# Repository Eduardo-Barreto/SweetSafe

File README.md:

# SweetSafe

Este repositório contém os arquivos do esquemático e da PCB do projeto SweetSafe, um "cofre" de doces com Raspberry Pi Pico. Inclui uma descrição dos componentes utilizados e instruções para montagem.

O funcionamento do SweetSafe é simples: a Raspberry Pi Pico controla um eletroímã que mantém a caixa de doces fechada. Quando um pagamento é realizado com sucesso, a Raspberry Pi Pico desativa o eletroímã, permitindo que a caixa seja aberta. Neste momento, LEDs indicam visualmente que a caixa está destravada, enquanto um buzzer emite um som indicando o sucesso da transação. Caso haja uma tentativa de acesso não autorizada, um sensor de fim de curso detecta a abertura da caixa e aciona um alarme, enquanto a Raspberry Pi Pico envia uma notificação aos servidores. Assim, o SweetSafe não apenas mantém os doces seguros, mas também fornece um sistema de monitoramento eficiente para proteger seu conteúdo.

## Pastas e Arquivos

- **kicad/**: Contém os arquivos de esquemático e PCB do projeto, bem como o principal do KiCad

  - `SweetSafe.kicad_pro`: Arquivo do KiCad
  - `SweetSafe.kicad_sch`: Esquemático do projeto
  - `SweetSafe.kicad_pcb`: Layout para a PCB do projeto

- **BOM.csv**: Lista de materiais do projeto.

- **images/**: Contém as imagens do projeto

## Imagens

### Esquemático

### PCB

### Visão 3D

3D com RayTracing (porque é maneiro)

## BOM (Bill of Materials)

| Designator           | Footprint                                          | Quantity |
| -------------------- | -------------------------------------------------- | -------- |
| Switch fim de curso  | SW_MS0850502F030P1A                                | 1        |
| Resistor 220 ohms    | R_Axial_DIN0414_L11.9mm_D4.5mm_P15.24mm_Horizontal | 2        |
| Resistor 10k ohms    | R_Axial_DIN0414_L11.9mm_D4.5mm_P15.24mm_Horizontal | 1        |
| Buzzer               | Buzzer_15x7.5RM7.6                                 | 1        |
| Transistor NPN BC337 | TO-92_Inline_Wide                                  | 1        |
| Raspberry Pi Pico W  | RPi_Pico_SMD_TH                                    | 1        |
| Conector Barrel Jack | BarrelJack_Horizontal                              | 1        |
| Header Fêmea 1x02    | PinSocket_1x02_P2.54mm_Horizontal                  | 3        |

## Gerbers

Os arquivos Gerber estão disponíveis na última release e na pasta `/kicad/gerbers`

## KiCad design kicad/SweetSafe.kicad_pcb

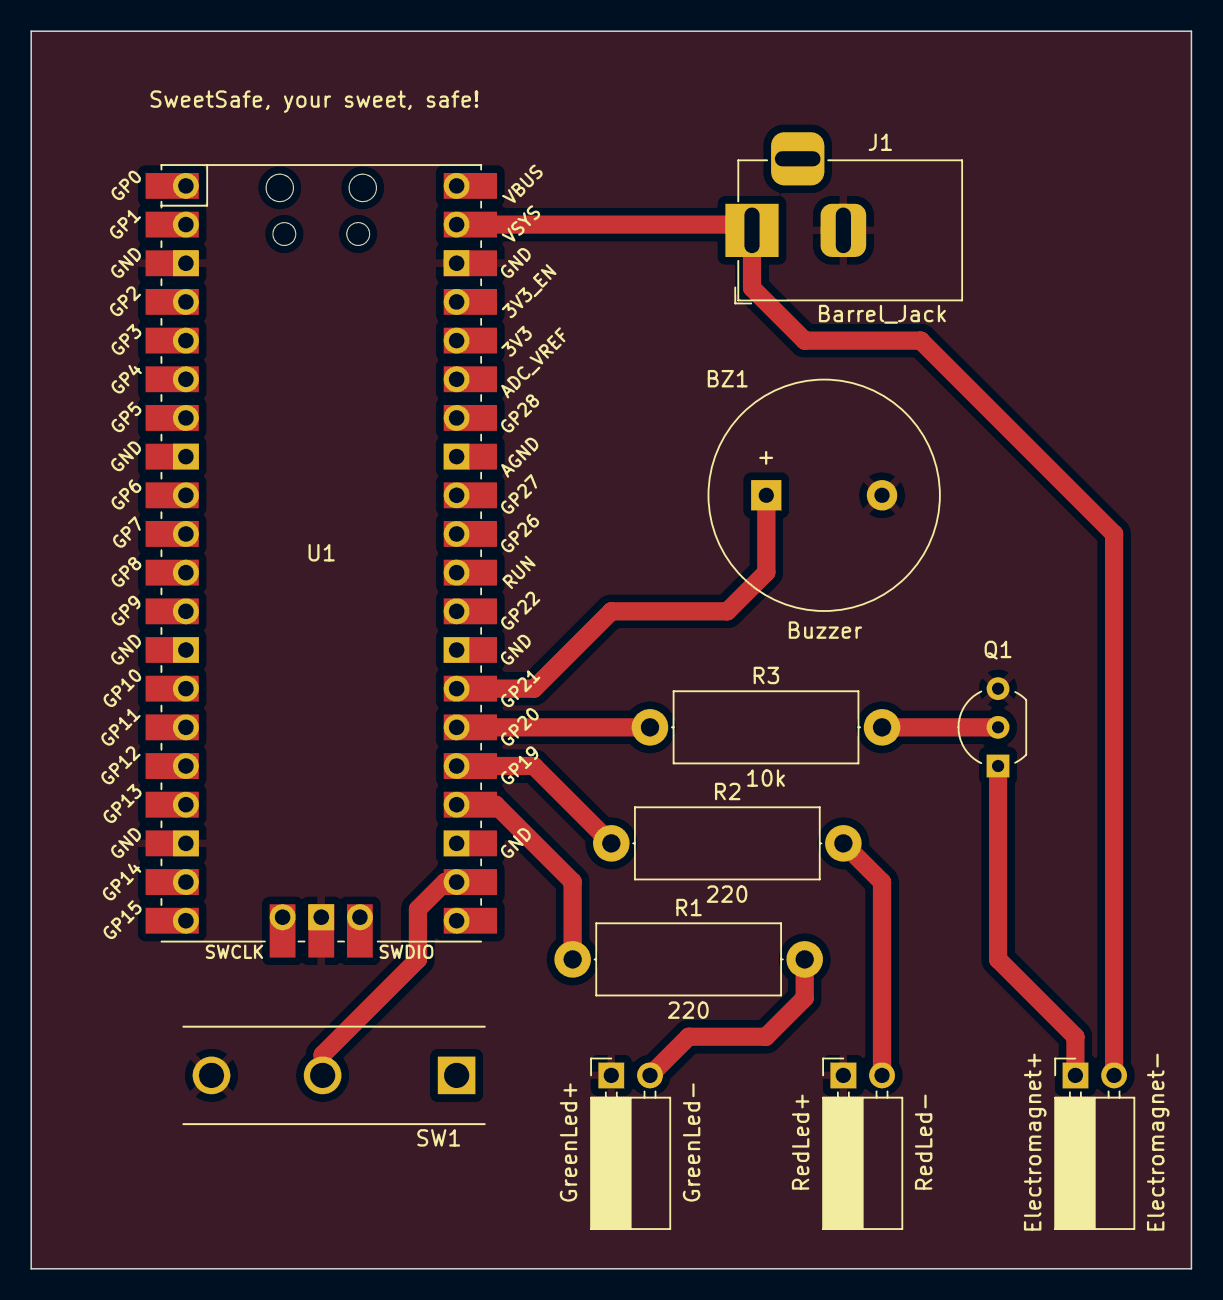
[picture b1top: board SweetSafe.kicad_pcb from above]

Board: 2 copper layers, 76.2 x 81.3 mm, 11 parts (0 on the bottom side), 11 nets.

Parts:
BZ1: Buzzer; Buzzer_15x7.5RM7.6
Electromagnet+: Electromagnet-; PinSocket_1x02_P2.54mm_Horizontal
GreenLed+: GreenLed-; PinSocket_1x02_P2.54mm_Horizontal
J1: Barrel_Jack; BarrelJack_Horizontal
Q1: BC337; TO-92_Inline_Wide
R1, R2: 220; R_Axial_DIN0414_L11.9mm_D4.5mm_P15.24mm_Horizontal
R3: 10k; R_Axial_DIN0414_L11.9mm_D4.5mm_P15.24mm_Horizontal
RedLed+: RedLed-; PinSocket_1x02_P2.54mm_Horizontal
SW1: SW_DPDT_x2; SW_MS0850502F030P1A
U1: Pico; RPi_Pico_SMD_TH

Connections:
Buzzer: BZ1.1 (+), U1.27 (GPIO21)
Electromagnet: R3.1, U1.26 (GPIO20)
GND: BZ1.2 (-), GreenLed+.1, J1.2, Q1.3 (E), RedLed+.1, SW1.2 (B), U1.3 (GND), U1.18 (GND), U1.38 (GND), U1.42 (GND)
GreenLed: R1.1, U1.24 (GPIO18)
unnamed: Electromagnet+.1, Q1.1 (C)
unnamed: GreenLed+.2, R1.2
unnamed: Q1.2 (B), R3.2
unnamed: R2.2, RedLed+.2
RedLed: R2.1, U1.25 (GPIO19)
Switch: SW1.3 (C), U1.22 (GPIO17)
VCC: Electromagnet+.2, J1.1, U1.39 (VSYS)

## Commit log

2024-04-01 :tada: Add kicad files and readme
2024-04-01 :feat: Add functional description
2024-04-01 :bug: Fix caption line
